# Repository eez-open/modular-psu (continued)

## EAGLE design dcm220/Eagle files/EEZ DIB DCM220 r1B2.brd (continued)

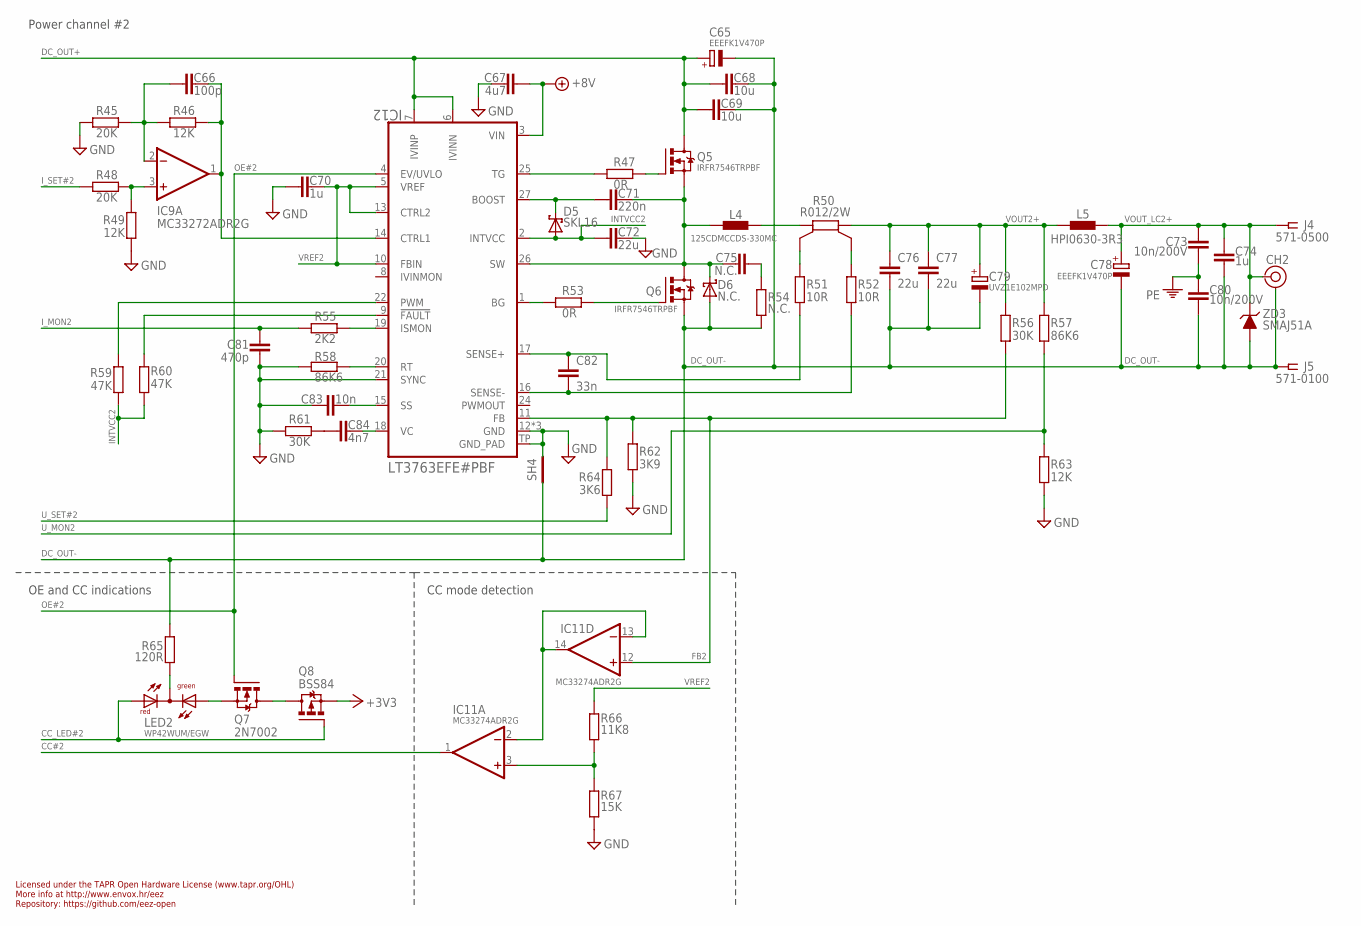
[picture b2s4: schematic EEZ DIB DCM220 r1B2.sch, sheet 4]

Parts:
C65, C78: EEEFK1V470P; CAPAE830X1050N
C66: 100p; C0805
C67: 4u7; C1206
C68, C69: 10u; C1210
C70, C74: 1u; C0805
C71: 220n; C0805
C72, C76, C77: 22u; C1210
C73, C80: 10n/200V; C1206
C75: N.C.; C0805
C79: UVZ1E102MPD; ECAP5/10.5
C81: 470p; C0805
C82: 33n; C0805
C83: 10n; C0805
C84: 4n7; C0805
CH2: TEST_POINT-2; TP_1.1MM_2
D5: SKL16; SOD123
D6: N.C.; SMA
IC9: MC33272ADR2G; SOIC127P600X173-8N
IC11: MC33274ADR2G; SOIC127P600X175-14N
IC12: LT3763EFE#PBF; LTC_05-08-1663-EB
J4: 571-0500; DELTRON_571
J5: 571-0100; DELTRON_571
L4: 125CDMCCDS-330MC; 125CDMCC/DS
L5: HPI0630-3R3; COILCRAFT_HPI0630
LED2: WP42WUM/EGW; L-42WUM-1EGWT
Q5, Q6: IRFR7546TRPBF; TO229P990X239-3N
Q7: 2N7002; SOT103P240X110-3N
Q8: BSS84; SOT95P237X112-3N
R45, R48: 20K; R0805
R46, R49, R63: 12K; R0805
R47, R53: 0R; R0805
R50: R012/2W; R_2512-4WIRE
R51, R52: 10R; R0805
R54: N.C.; R1206
R55: 2K2; R0805
R56, R61: 30K; R0805
R57, R58: 86K6; R0805
R59, R60: 47K; R0805
R62: 3K9; R0805
R64: 3K6; R0805
R65: 120R; R0805
R66: 11K8; R0805
R67: 15K; R0805
SH4: SHORTNOHOLE; SHORT_NOHOLE
ZD3: SMAJ51A; DO214AA

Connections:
+3V3: Q8.2 (S); also elsewhere on the board
+8V: C67.1, IC12.3 (VIN); also elsewhere on the board
CC#2: IC11.1 (OUT); also elsewhere on the board
CC_LED#2: LED2.RED (AR), Q8.1 (G); also elsewhere on the board
DC_OUT+: C65.+, C68.1, C69.1, IC12.6 (IVINN), IC12.7 (IVINP), Q5.2 (D); also elsewhere on the board
DC_OUT-: C65.-, C68.2, C69.2, C74.2, C76.2, C77.2, C78.-, C79.-, C80.2, CH2.GND, D6.A, J5.1, J5.1.1, Q6.3 (S), R54.1, R65.2, SH4.1 (GND_A), ZD3.A; also elsewhere on the board
FB2: IC11.12 (+IN), IC12.11 (FB), R56.1, R62.2, R64.2
GND: C67.2, C70.2, C72.2, C81.1, C83.1, IC12.12 (GND), IC12.21 (SYNC), IC12.23 (GND), IC12.28 (GND), IC12.TP (GND_PAD), R45.1, R49.1, R58.1, R61.1, R62.1, R63.1, R67.1, SH4.2 (GND_B); also elsewhere on the board
INTVCC2: C72.1, D5.A, IC12.2 (INTVCC), R59.1, R60.2
I_MON2: C81.2, R55.1; also elsewhere on the board
I_SET#2: R48.1; also elsewhere on the board
LOUT2: L4.2, R50.1
unnamed: IC12.20 (RT), R58.2
unnamed: LED2.CC (C), R65.1
unnamed: C83.2, IC12.15 (SS)
unnamed: C84.1, R61.2
unnamed: Q7.3 (D), Q8.3 (D)
unnamed: LED2.GREEN (AG), Q7.2 (S)
unnamed: C84.2, IC12.18 (VC)
unnamed: IC12.9 (!FAULT), R60.1
unnamed: IC12.25 (TG), R47.1
unnamed: Q5.1 (G), R47.2
unnamed: IC12.1 (BG), R53.1
unnamed: Q6.1 (G), R53.2
unnamed: R50.1S, R51.2
unnamed: R50.2S, R52.2
unnamed: C75.2, R54.2
unnamed: C71.1, D5.C, IC12.27 (BOOST)
unnamed: IC12.19 (ISMON), R55.2
unnamed: IC11.2 (-IN), IC11.13 (-IN), IC11.14 (OUT)
unnamed: IC11.3 (+IN), R66.1, R67.2
unnamed: C66.1, IC9.1 (OUT), IC12.14 (CTRL1), R46.2
unnamed: C66.2, IC9.2 (-IN), R45.2, R46.1
unnamed: IC9.3 (+IN), R48.2, R49.2
OE#2: IC12.4 (EV/UVLO), Q7.1 (G); also elsewhere on the board
PE: C73.1, C80.1; also elsewhere on the board
PWM#2: IC12.22 (PWM), R59.2
SENSE1+1: C82.1, IC12.17 (SENSE+), R51.1
SENSE1-1: C82.2, IC12.16 (SENSE-), R52.1
SW2: C71.2, C75.1, D6.C, IC12.26 (SW), L4.1, Q5.3 (S), Q6.2 (D)
U_MON2: R57.1, R63.2; also elsewhere on the board
U_SET#2: R64.1; also elsewhere on the board
VOUT2+: C76.1, C77.1, C79.+, L5.1, R50.2, R56.2, R57.2
VOUT_LC2+: C73.2, C74.1, C78.+, CH2.TIP, J4.1, J4.1.1, L5.2, ZD3.C
VREF2: C70.1, IC12.5 (VREF), IC12.10 (FBIN), IC12.13 (CTRL2), R66.2

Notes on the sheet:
Licensed under the TAPR Open Hardware License (www.tapr.org/OHL)
Repository: https://github.com/eez-open
More info at http://www.envox.hr/eez
CC mode detection
OE and CC indications
Power channel #2

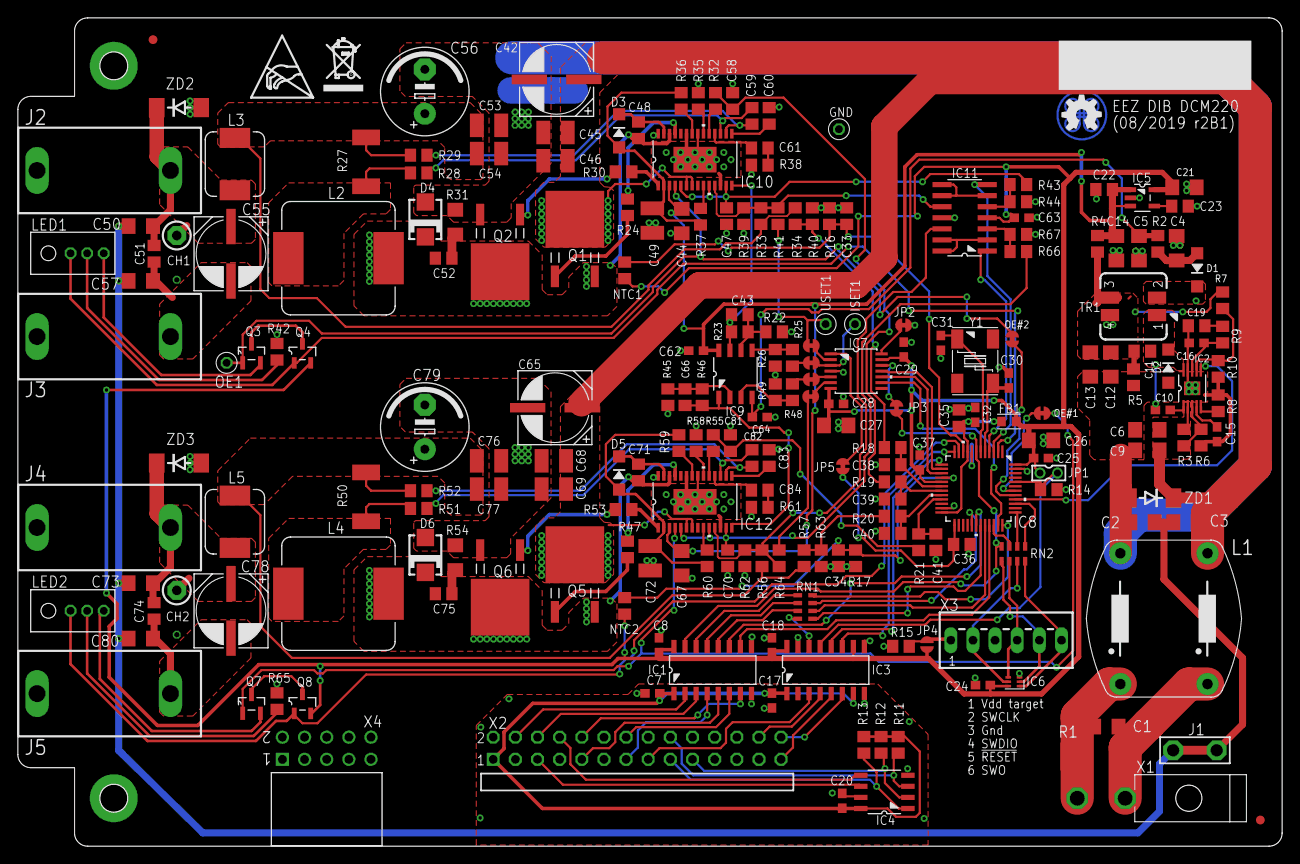
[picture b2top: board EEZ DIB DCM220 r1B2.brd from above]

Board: 2 copper layers, 145.0 x 95.0 mm, 231 parts (1 on the bottom side), 165 nets.

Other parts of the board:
EEZ_SIGNATURE: SIGNATURESMALL; SIGNATURE_5MM
U$2: RECYCLE_BIN1/8
U$4: ESD_SYMBOL

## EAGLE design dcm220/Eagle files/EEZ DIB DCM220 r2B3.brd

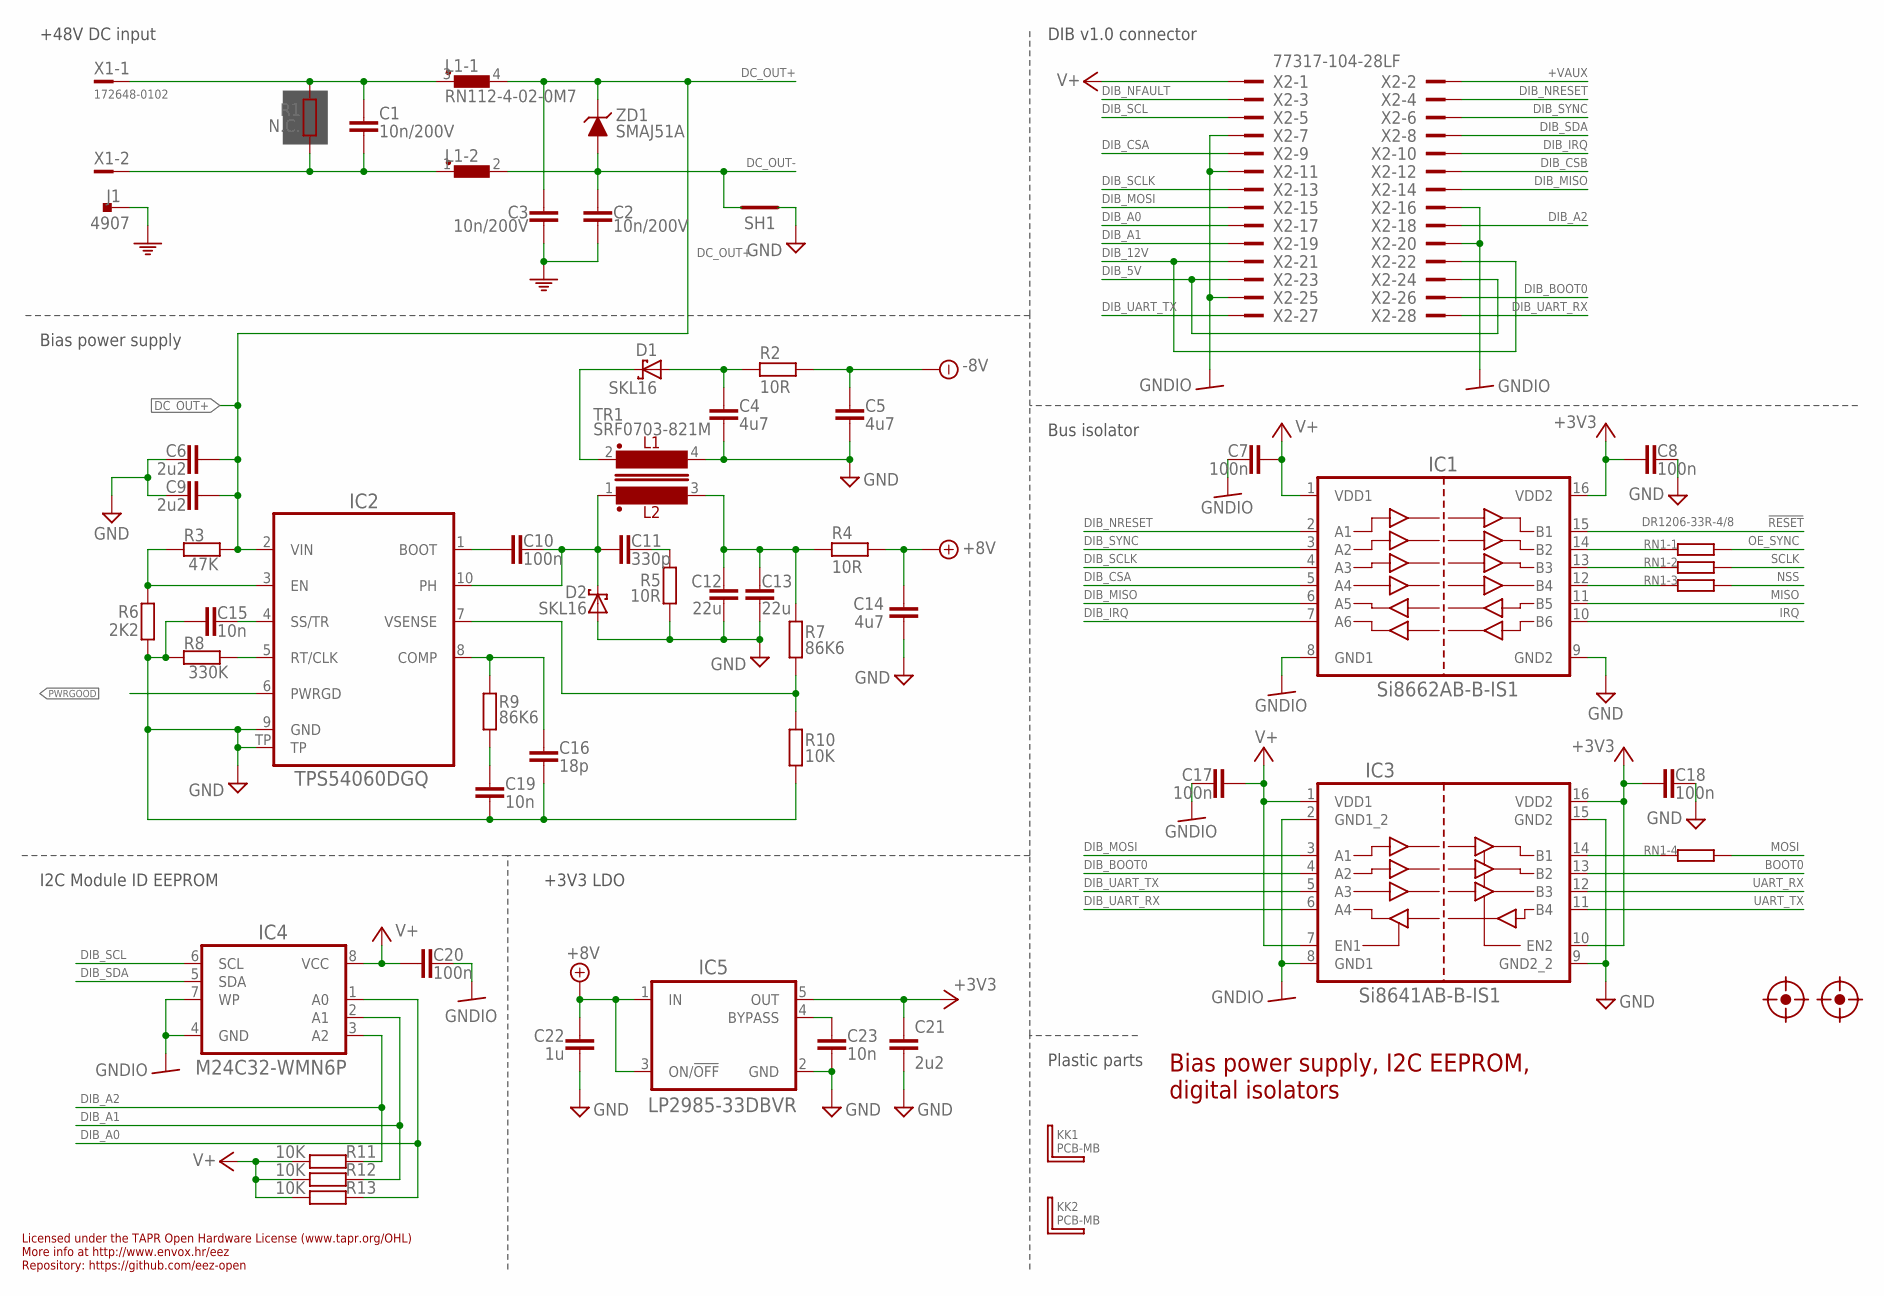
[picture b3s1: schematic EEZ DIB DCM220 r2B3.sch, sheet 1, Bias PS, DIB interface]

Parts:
C1, C2, C3: 10n/200V; C1206
C4, C5, C14: 4u7; C1206
C6, C9, C21: 2u2; C1206
C7, C8, C10, C17, C18, C20: 100n; C0603
C11: 330p; C0805
C12, C13: 22u; C1206
C15, C19, C23: 10n; C0805
C16: 18p; C0603
C22: 1u; C0805
D1, D2: SKL16; SOD123
FM1, FM2: FIDUCIAL_2; FIDUCIAL_DUAL
IC1: Si8662AB-B-IS1; SOIC-16
IC2: TPS54060DGQ; SOP50P490X110-11N
IC3: Si8641AB-B-IS1; SOIC-16
IC4: M24C32-WMN6P; SOIC127P600X173-8N
IC5: LP2985-33DBVR; SOT95P270X145-5N
J1: 4907; PCB_TAB-4907
KK1, KK2: PCB-MB
L1: RN112-4-02-0M7; RN112
R1: N.C.; R2512
R2, R4, R5: 10R; R0805
R3: 47K; R0805
R6: 2K2; R0805
R7, R9: 86K6; R0805
R8: 330K; R0805
R10, R11, R12, R13: 10K; R0805
RN1: DR1206-33R-4/8; CAY16
SH1: SHORTNOHOLE; SHORT_NOHOLE
TR1: SRF0703-821M; SRF0703
X1: 172648-0102; MINIFIT_39301020
X2: 77317-104-28LF
ZD1: SMAJ51A; DO214AA

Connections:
!RESET: IC1.15 (B1); also elsewhere on the board
+3V3: C8.2, C18.2, C21.1, IC1.16 (VDD2), IC3.10 (EN2), IC3.16 (VDD2), IC5.5 (OUT); also elsewhere on the board
+8V: C14.1, C22.2, IC5.1 (IN), IC5.3 (ON/!OFF), R4.1; also elsewhere on the board
+VAUX: X2.2
-8V: C5.1, R2.1; also elsewhere on the board
BOOT0: IC3.13 (B2); also elsewhere on the board
DC+: C1.2, L1.3 (1), R1.2, X1.1
DC-: C1.1, L1.1, R1.1, X1.2
DC_OUT+: C3.2, C6.1, C9.1, IC2.2 (VIN), L1.4 (2), R3.2, ZD1.C; also elsewhere on the board
DC_OUT-: C2.1, L1.2, SH1.2 (GND_B), ZD1.A; also elsewhere on the board
DIB_5V: X2.23, X2.24
DIB_12V: X2.21, X2.22
DIB_A0: IC4.1 (A0), R13.2, X2.17
DIB_A1: IC4.2 (A1), R12.2, X2.19
DIB_A2: IC4.3 (A2), R11.2, X2.18
DIB_BOOT0: IC3.4 (A2), X2.26
DIB_CSA: IC1.5 (A4), X2.9
DIB_CSB: X2.12
DIB_IRQ: IC1.7 (A6), X2.10
DIB_MISO: IC1.6 (A5), X2.14
DIB_MOSI: IC3.3 (A1), X2.15
DIB_NFAULT: X2.3
DIB_NRESET: IC1.2 (A1), X2.4
DIB_SCL: IC4.6 (SCL), X2.5
DIB_SCLK: IC1.4 (A3), X2.13
DIB_SDA: IC4.5 (SDA), X2.8
DIB_SYNC: IC1.3 (A2), X2.6
DIB_UART_RX: IC3.6 (A4), X2.28
DIB_UART_TX: IC3.5 (A3), X2.27
GND: C4.2, C5.2, C6.2, C8.1, C9.2, C12.2, C13.2, C14.2, C15.2, C16.1, C18.1, C19.1, C21.2, C22.1, C23.1, D2.A, IC1.9 (GND2), IC2.9 (GND), IC2.TP, IC3.9 (GND2_2), IC3.15 (GND2), IC5.2 (GND), R5.1, R6.1, R8.1, R10.1, SH1.1 (GND_A), TR1.4; also elsewhere on the board
GNDIO: C7.2, C17.2, C20.1, IC1.8 (GND1), IC3.2 (GND1_2), IC3.8 (GND1), IC4.4 (GND), IC4.7 (WP), X2.7, X2.11, X2.16, X2.20, X2.25
IRQ: IC1.10 (B6); also elsewhere on the board
MISO: IC1.11 (B5); also elsewhere on the board
MOSI: RN1.5 (2); also elsewhere on the board
unnamed: IC1.14 (B2), RN1.1
unnamed: IC1.13 (B3), RN1.2 (1)
unnamed: IC1.12 (B4), RN1.3 (1)
unnamed: IC3.14 (B1), RN1.4 (1)
unnamed: C23.2, IC5.4 (BYPASS)
unnamed: C4.1, D1.A, R2.2
unnamed: C11.2, R5.2
unnamed: IC2.3 (EN), R3.1, R6.2
unnamed: C15.1, IC2.4 (SS/TR)
unnamed: IC2.5 (RT/CLK), R8.2
unnamed: C16.2, IC2.8 (COMP), R9.2
unnamed: C19.2, R9.1
unnamed: C10.2, IC2.1 (BOOT)
unnamed: IC2.7 (VSENSE), R7.1, R10.2
NSS: RN1.6 (2); also elsewhere on the board
OE_SYNC: RN1.8 (2); also elsewhere on the board
PE: C2.2, C3.1, J1.1, J1.2; also elsewhere on the board
PH1: C10.1, C11.1, D2.C, IC2.10 (PH), TR1.1
PWRGOOD: IC2.6 (PWRGD); also elsewhere on the board
SCLK: RN1.7 (2); also elsewhere on the board
UART_RX: IC3.12 (B3); also elsewhere on the board
UART_TX: IC3.11 (B4); also elsewhere on the board
V+: C7.1, C17.1, C20.2, IC1.1 (VDD1), IC3.1 (VDD1), IC3.7 (EN1), IC4.8 (VCC), R11.1, R12.1, R13.1, X2.1
VOUT+: C12.1, C13.1, R4.2, R7.2, TR1.3
VOUT-: D1.C, TR1.2

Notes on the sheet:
Licensed under the TAPR Open Hardware License (www.tapr.org/OHL)
Repository: https://github.com/eez-open
More info at http://www.envox.hr/eez
I2C Module ID EEPROM
Bias power supply, I2C EEPROM, digital isolators
Plastic parts
Bus isolator
+3V3 LDO
DIB v1.0 connector
Bias power supply
+48V DC input

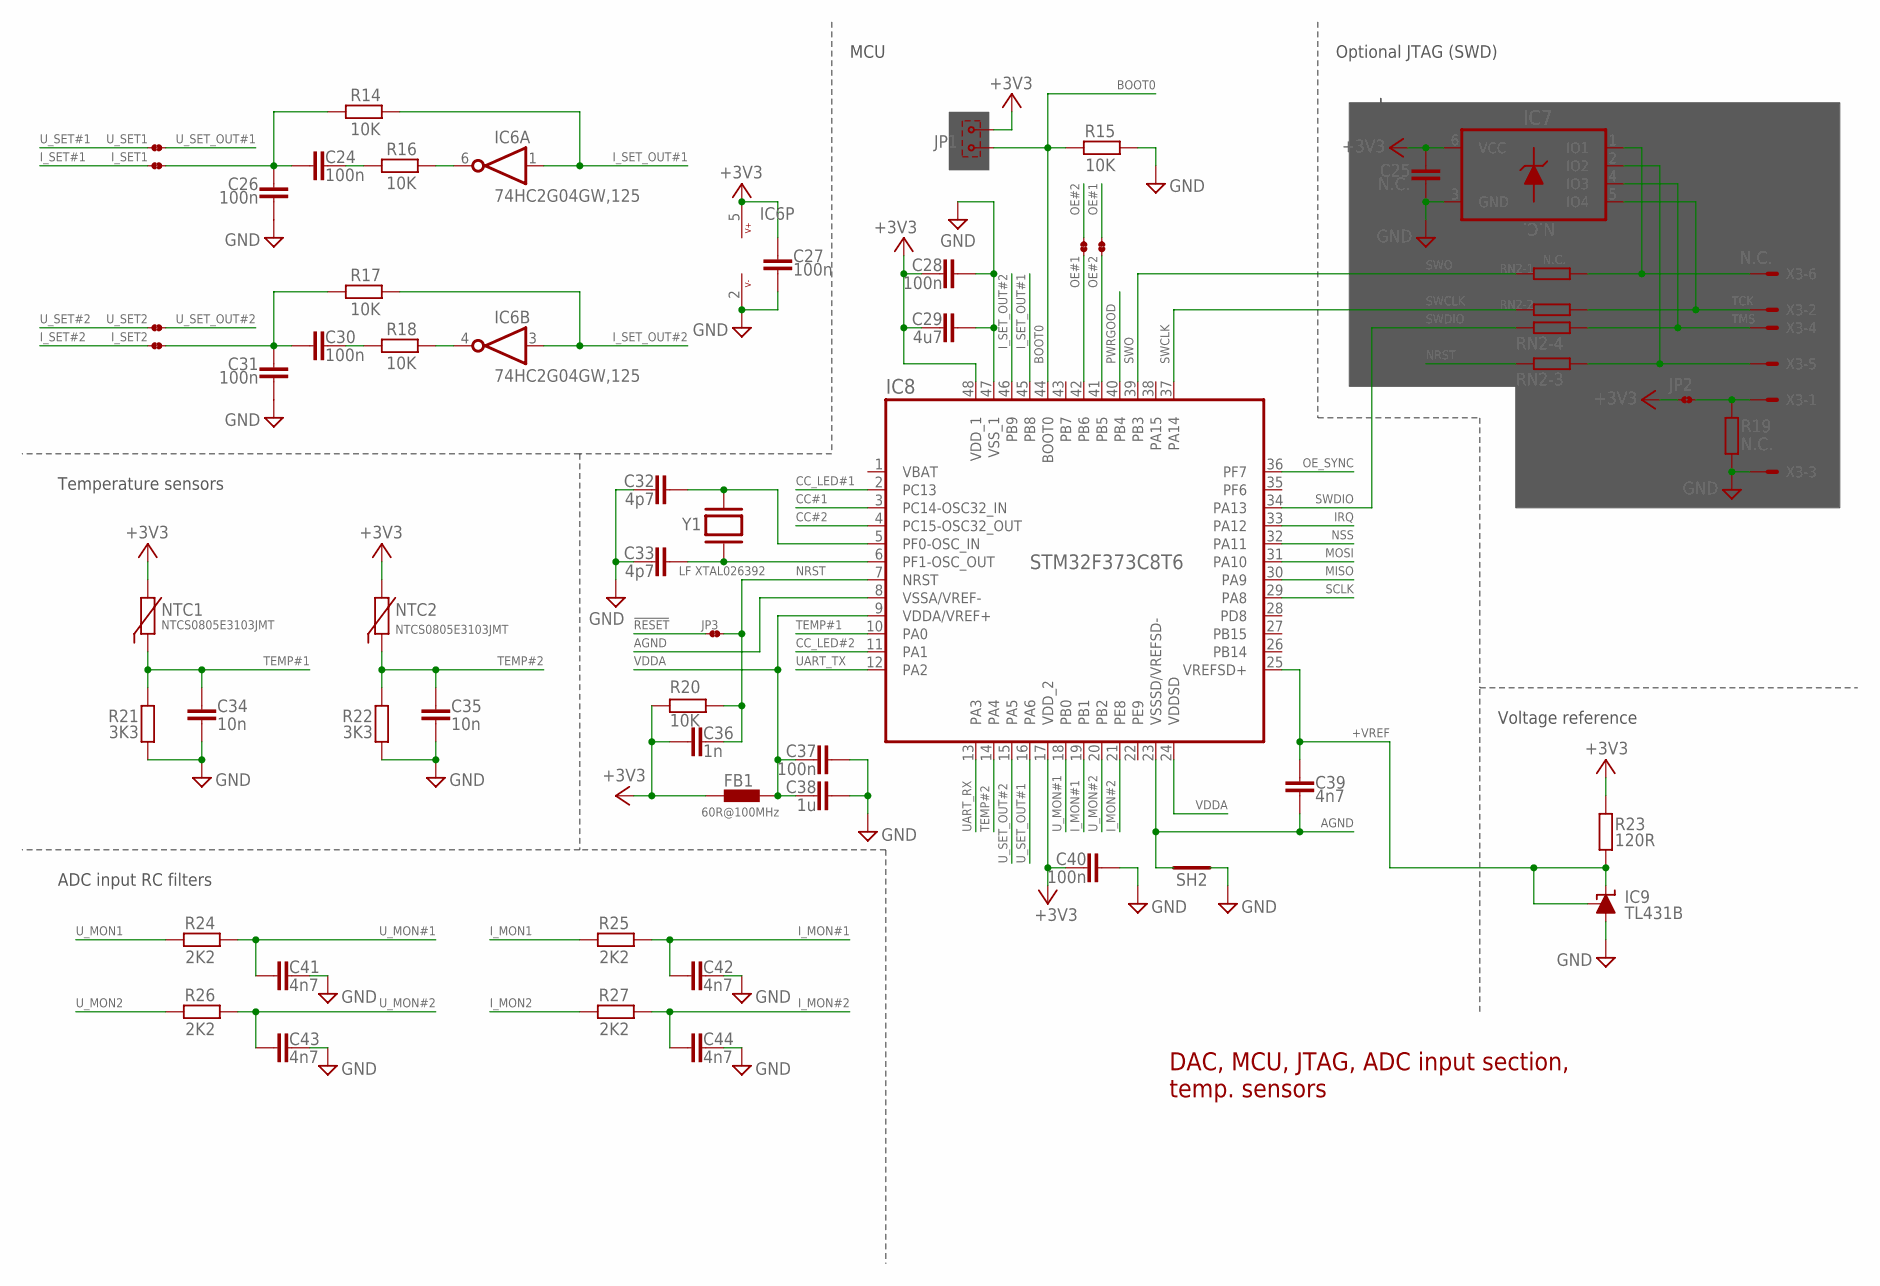
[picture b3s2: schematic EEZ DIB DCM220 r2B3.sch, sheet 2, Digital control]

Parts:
C24, C26, C27, C28, C30, C31, C37, C40: 100n; C0603
C25: N.C.; C0603
C29: 4u7; C1206
C32, C33: 4p7; C0603
C34, C35: 10n; C0805
C36: 1n; C0805
C38: 1u; C0805
C39, C41, C42, C43, C44: 4n7; C0805
FB1: 60R@100MHz; BEAD0603
IC6: 74HC2G04GW,125; SOT65P210X110-6N
IC7: N.C.; DRL6
IC8: STM32F373C8T6; LQFP-48
IC9: TL431B; SOT103P240X110-3N
I_SET1, I_SET2: JP2-NOCUT
JP1: JUMPER-2PIN-2MM; 2MM-2
JP2: JP2-CUT
JP3: JP2-NOCUT
NTC1, NTC2: NTCS0805E3103JMT; R_0805
OE#1, OE#2: JP2-NOCUT
R14, R15, R16, R17, R18, R20: 10K; R0805
R19: N.C.; R0805
R21, R22: 3K3; R0805
R23: 120R; R0805
R24, R25, R26, R27: 2K2; R0805
RN2: N.C.; CAY16
SH2: SHORTNOHOLE; SHORT_NOHOLE
U_SET1, U_SET2: JP2-NOCUT
X3: N.C.; 22-23-2061
Y1: LF XTAL026392; 12SMX(B)

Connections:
!RESET: JP3.1; also elsewhere on the board
+3V3: C25.1, C27.1, C28.2, C29.1, C36.2, C40.2, FB1.P$1 (1), IC6.5 (V+), IC7.6 (VCC), IC8.17 (VDD_2), IC8.48 (VDD_1), JP1.1, JP2.1, NTC1.1, NTC2.1, R20.1, R23.1; also elsewhere on the board
+VREF: C39.2, IC8.25 (VREFSD+), IC9.1 (C), IC9.2 (R), R23.2
AGND: C39.1, IC8.8 (VSSA/VREF-), IC8.23 (VSSSD/VREFSD-), SH2.1 (GND_A)
BOOT0: IC8.44 (BOOT0), JP1.2, R15.2; also elsewhere on the board
CC#1: IC8.3 (PC14-OSC32_IN); also elsewhere on the board
CC#2: IC8.4 (PC15-OSC32_OUT); also elsewhere on the board
CC_LED#1: IC8.2 (PC13); also elsewhere on the board
CC_LED#2: IC8.11 (PA1); also elsewhere on the board
GND: C25.2, C26.2, C27.2, C28.1, C29.2, C31.2, C32.1, C33.1, C34.1, C35.1, C37.1, C38.1, C40.1, C41.1, C42.1, C43.1, C44.1, IC6.2 (V-), IC7.3 (GND), IC8.47 (VSS_1), IC9.3 (A), R15.1, R19.1, R21.2, R22.2, SH2.2 (GND_B), X3.3; also elsewhere on the board
IRQ: IC8.33 (PA12); also elsewhere on the board
I_MON1: R25.2; also elsewhere on the board
I_MON2: R27.2; also elsewhere on the board
I_MON#1: C42.2, IC8.19 (PB1), R25.1
I_MON#2: C44.2, IC8.21 (PE8), R27.1
I_SET#1: I_SET1.1; also elsewhere on the board
I_SET#2: I_SET2.1; also elsewhere on the board
I_SET_OUT#1: IC6.1 (I), IC8.45 (PB8), R14.2
I_SET_OUT#2: IC6.3 (I), IC8.46 (PB9), R17.2
MISO: IC8.30 (PA9); also elsewhere on the board
MOSI: IC8.31 (PA10); also elsewhere on the board
unnamed: C30.2, R18.1
unnamed: C30.1, C31.1, I_SET2.2, R17.1
unnamed: IC6.4 (O), R18.2
unnamed: IC7.1 (IO1), RN2.8 (2), X3.6
unnamed: IC7.2 (IO2), RN2.6 (2), X3.5
unnamed: JP2.2, R19.2, X3.1
unnamed: C24.2, R16.1
unnamed: C24.1, C26.1, I_SET1.2, R14.1
unnamed: IC6.6 (O), R16.2
unnamed: IC8.42 (PB6), OE#1.1
unnamed: IC8.41 (PB5), OE#2.1
NRST: C36.1, IC8.7 (NRST), JP3.2, R20.2, RN2.3 (1)
NSS: IC8.32 (PA11); also elsewhere on the board
OE#1: OE#2.2; also elsewhere on the board
OE#2: OE#1.2; also elsewhere on the board
OE_SYNC: IC8.36 (PF7); also elsewhere on the board
PWRGOOD: IC8.40 (PB4); also elsewhere on the board
RCC_OSC_IN: C32.2, IC8.5 (PF0-OSC_IN), Y1.3 (2)
RCC_OSC_OUT: C33.2, IC8.6 (PF1-OSC_OUT), Y1.1
SCLK: IC8.29 (PA8); also elsewhere on the board
SWCLK: IC8.37 (PA14), RN2.2 (1)
SWDIO: IC8.34 (PA13), RN2.4 (1)
SWO: IC8.39 (PB3), RN2.1
TCK: IC7.5 (IO4), RN2.7 (2), X3.2
TEMP#1: C34.2, IC8.10 (PA0), NTC1.2, R21.1
TEMP#2: C35.2, IC8.14 (PA4), NTC2.2, R22.1
TMS: IC7.4 (IO3), RN2.5 (2), X3.4
UART_RX: IC8.13 (PA3); also elsewhere on the board
UART_TX: IC8.12 (PA2); also elsewhere on the board
U_MON1: R24.2; also elsewhere on the board
U_MON2: R26.2; also elsewhere on the board
U_MON#1: C41.2, IC8.18 (PB0), R24.1
U_MON#2: C43.2, IC8.20 (PB2), R26.1
U_SET#1: U_SET1.1; also elsewhere on the board
U_SET#2: U_SET2.1; also elsewhere on the board
U_SET_OUT#1: IC8.16 (PA6), U_SET1.2
U_SET_OUT#2: IC8.15 (PA5), U_SET2.2
VDDA: C37.2, C38.2, FB1.P$2 (2), IC8.9 (VDDA/VREF+), IC8.24 (VDDSD)

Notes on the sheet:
DAC, MCU, JTAG, ADC input section, temp. sensors
Optional JTAG (SWD)
MCU
Temperature sensors
ADC input RC filters
Voltage reference

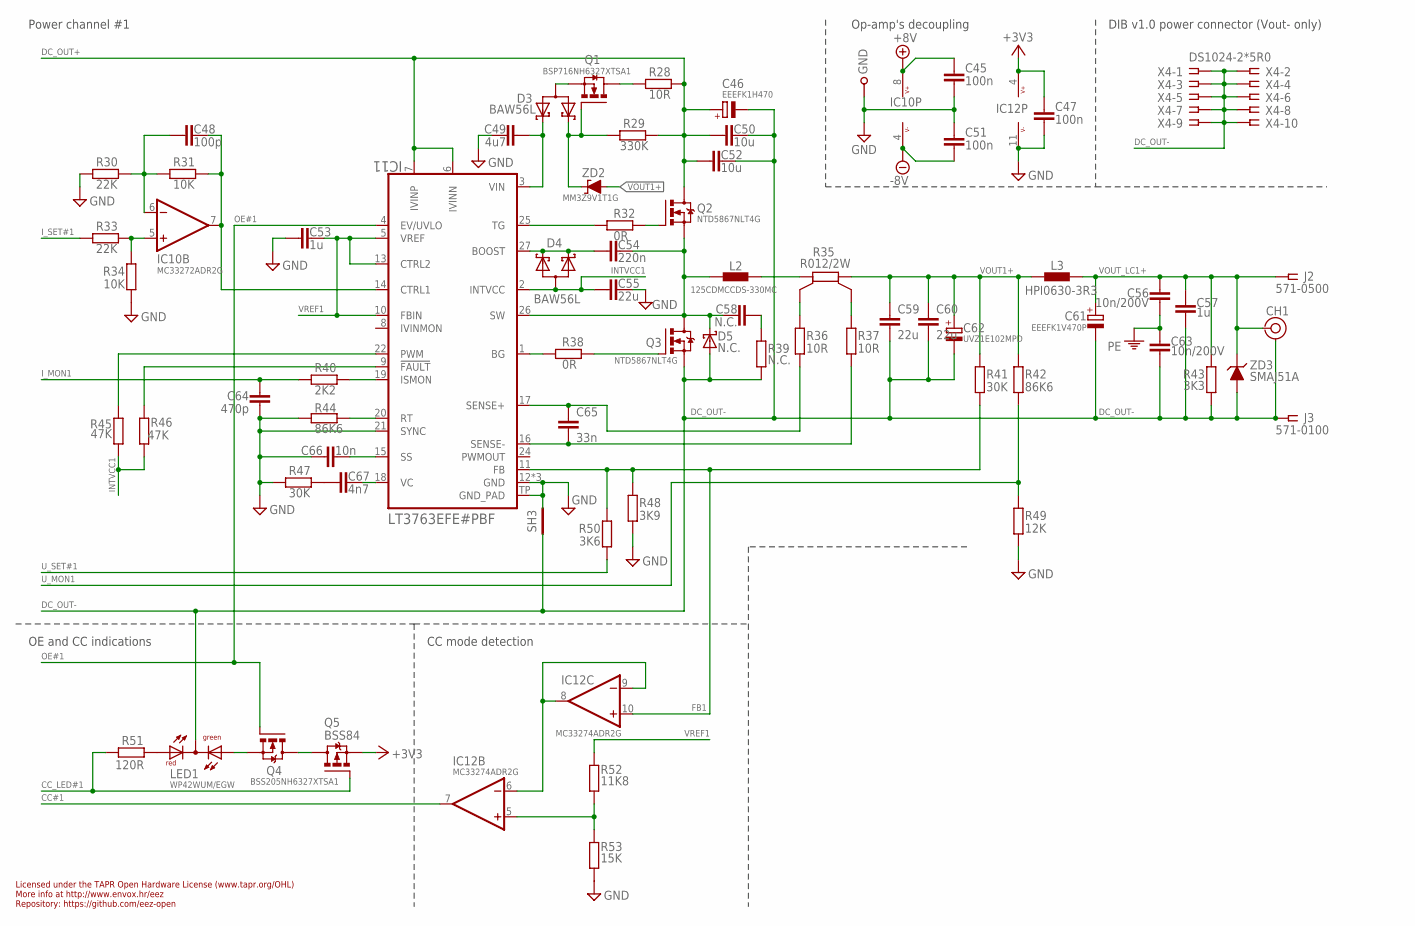
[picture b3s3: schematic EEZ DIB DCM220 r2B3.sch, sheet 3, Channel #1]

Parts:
C45, C47, C51: 100n; C0603
C46: EEEFK1H470; CAPAE830X1050N
C48: 100p; C0805
C49: 4u7; C1206
C50, C52: 10u; C1210
C53, C57: 1u; C0805
C54: 220n; C0805
C55, C59, C60: 22u; C1210
C56, C63: 10n/200V; C1206
C58: N.C.; C0805
C61: EEEFK1V470P; CAPAE660X610N
C62: UVZ1E102MPD; ECAP5/10.5
C64: 470p; C0805
C65: 33n; C0805
C66: 10n; C0805
C67: 4n7; C0805
CH1: TEST_POINT-2; TP_1.1MM_2
D3, D4: BAW56L; SOT23
D5: N.C.; SMA
GND: TEST-PIN_0.9MM
IC10: MC33272ADR2G; SOIC127P600X173-8N
IC11: LT3763EFE#PBF; LTC_05-08-1663-EB
IC12: MC33274ADR2G; SOIC127P600X175-14N
J2: 571-0500; DELTRON_571
J3: 571-0100; DELTRON_571
L2: 125CDMCCDS-330MC; 125CDMCC/DS
L3: HPI0630-3R3; COILCRAFT_HPI0630
LED1: WP42WUM/EGW; L-42WUM-1EGWT
Q1: BSP716NH6327XTSA1; SOT223
Q2, Q3: NTD5867NLT4G; TO229P990X239-3N
Q4: BSS205NH6327XTSA1; SOT103P240X110-3N
Q5: BSS84; SOT95P237X112-3N
R28, R36, R37: 10R; R0805
R29: 330K; R0805
R30, R33: 22K; R0805
R31, R34: 10K; R0805
R32, R38: 0R; R0805
R35: R012/2W; R_2512-4WIRE
R39: N.C.; R1206
R40: 2K2; R0805
R41, R47: 30K; R0805
R42, R44: 86K6; R0805
R43: 3K3; R0805
R45, R46: 47K; R0805
R48: 3K9; R0805
R49: 12K; R0805
R50: 3K6; R0805
R51: 120R; R0805
R52: 11K8; R0805
R53: 15K; R0805
SH3: SHORTNOHOLE; SHORT_NOHOLE
X4: DS1024-2*5R0; SSW-105-02-T-D-RA
ZD2: MM3Z9V1T1G; SOD323-W
ZD3: SMAJ51A; DO214AA

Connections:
+3V3: C47.1, IC12.4 (V+), Q5.2 (S); also elsewhere on the board
+8V: C45.1, IC10.8 (V+); also elsewhere on the board
-8V: C51.2, IC10.4 (V-); also elsewhere on the board
CC#1: IC12.7 (OUT); also elsewhere on the board
CC_LED#1: Q5.1 (G), R51.2; also elsewhere on the board
DC_OUT+: C46.+, C50.1, C52.1, IC11.6 (IVINN), IC11.7 (IVINP), Q2.2 (D), R28.1, R29.1; also elsewhere on the board
DC_OUT-: C46.-, C50.2, C52.2, C57.2, C59.2, C60.2, C61.2 (-), C62.-, C63.2, CH1.GND, D5.A, J3.1, J3.1.1, LED1.CC (C), Q3.3 (S), R39.1, R43.2, SH3.1 (GND_A), X4.1, X4.2, X4.3, X4.4, X4.5, X4.6, X4.7, X4.8, X4.9, X4.10, ZD3.A; also elsewhere on the board
FB1: IC11.11 (FB), IC12.10 (+IN), R41.1, R48.2, R50.2
GND: C45.2, C47.2, C49.2, C51.1, C53.2, C55.2, C64.1, C66.1, GND.1, IC11.12 (GND), IC11.21 (SYNC), IC11.23 (GND), IC11.28 (GND), IC11.TP (GND_PAD), IC12.11 (V-), R30.1, R34.1, R44.1, R47.1, R48.1, R49.1, R53.1, SH3.2 (GND_B); also elsewhere on the board
INTVCC1: C55.1, D4.3 (CA), IC11.2 (INTVCC), R45.1, R46.2
ISET1: C48.1, IC10.7 (OUT), IC11.14 (CTRL1), R31.2
I_MON1: C64.2, R40.1; also elsewhere on the board
I_SET#1: R33.1; also elsewhere on the board
LOUT1: L2.2, R35.1
unnamed: IC11.1 (BG), R38.1
unnamed: Q3.1 (G), R38.2
unnamed: Q4.3 (D), Q5.3 (D)
unnamed: R35.1S, R36.2
unnamed: IC11.20 (RT), R44.2
unnamed: LED1.RED (AR), R51.1
unnamed: C66.2, IC11.15 (SS)
unnamed: C67.1, R47.2
unnamed: C67.2, IC11.18 (VC)
unnamed: IC11.25 (TG), R32.1
unnamed: R35.2S, R37.2
unnamed: C58.2, R39.2
unnamed: IC11.9 (!FAULT), R46.1
unnamed: Q2.1 (G), R32.2
unnamed: C54.1, D4.1 (K1), D4.2 (K2), IC11.27 (BOOST)
unnamed: D3.1 (K1), Q1.1 (G), R29.2, ZD2.C
unnamed: LED1.GREEN (AG), Q4.2 (S)
unnamed: C49.1, D3.2 (K2), IC11.3 (VIN)
unnamed: D3.3 (CA), Q1.3 (S)
unnamed: IC11.19 (ISMON), R40.2
unnamed: IC12.5 (+IN), R52.1, R53.2
unnamed: IC12.6 (-IN), IC12.8 (OUT), IC12.9 (-IN)
unnamed: IC10.5 (+IN), R33.2, R34.2
unnamed: C48.2, IC10.6 (-IN), R30.2, R31.1
OE#1: IC11.4 (EV/UVLO), Q4.1 (G); also elsewhere on the board
PE: C56.1, C63.1; also elsewhere on the board
PWM#1: IC11.22 (PWM), R45.2
Q1D: Q1.2 (D), Q1.4 (D), R28.2
SENSE1+: C65.1, IC11.17 (SENSE+), R36.1
SENSE1-: C65.2, IC11.16 (SENSE-), R37.1
SW1: C54.2, C58.1, D5.C, IC11.26 (SW), L2.1, Q2.3 (S), Q3.2 (D)
U_MON1: R42.1, R49.2; also elsewhere on the board
U_SET#1: R50.1; also elsewhere on the board
VOUT1+: C59.1, C60.1, C62.+, L3.1, R35.2, R41.2, R42.2, ZD2.A
VOUT_LC1+: C56.2, C57.1, C61.1 (+), CH1.TIP, J2.1, J2.1.1, L3.2, R43.1, ZD3.C
VREF1: C53.1, IC11.5 (VREF), IC11.10 (FBIN), IC11.13 (CTRL2), R52.2

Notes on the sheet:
Licensed under the TAPR Open Hardware License (www.tapr.org/OHL)
Repository: https://github.com/eez-open
More info at http://www.envox.hr/eez
Power channel #1
CC mode detection
DIB v1.0 power connector (Vout- only)
Op-amp's decoupling
OE and CC indications

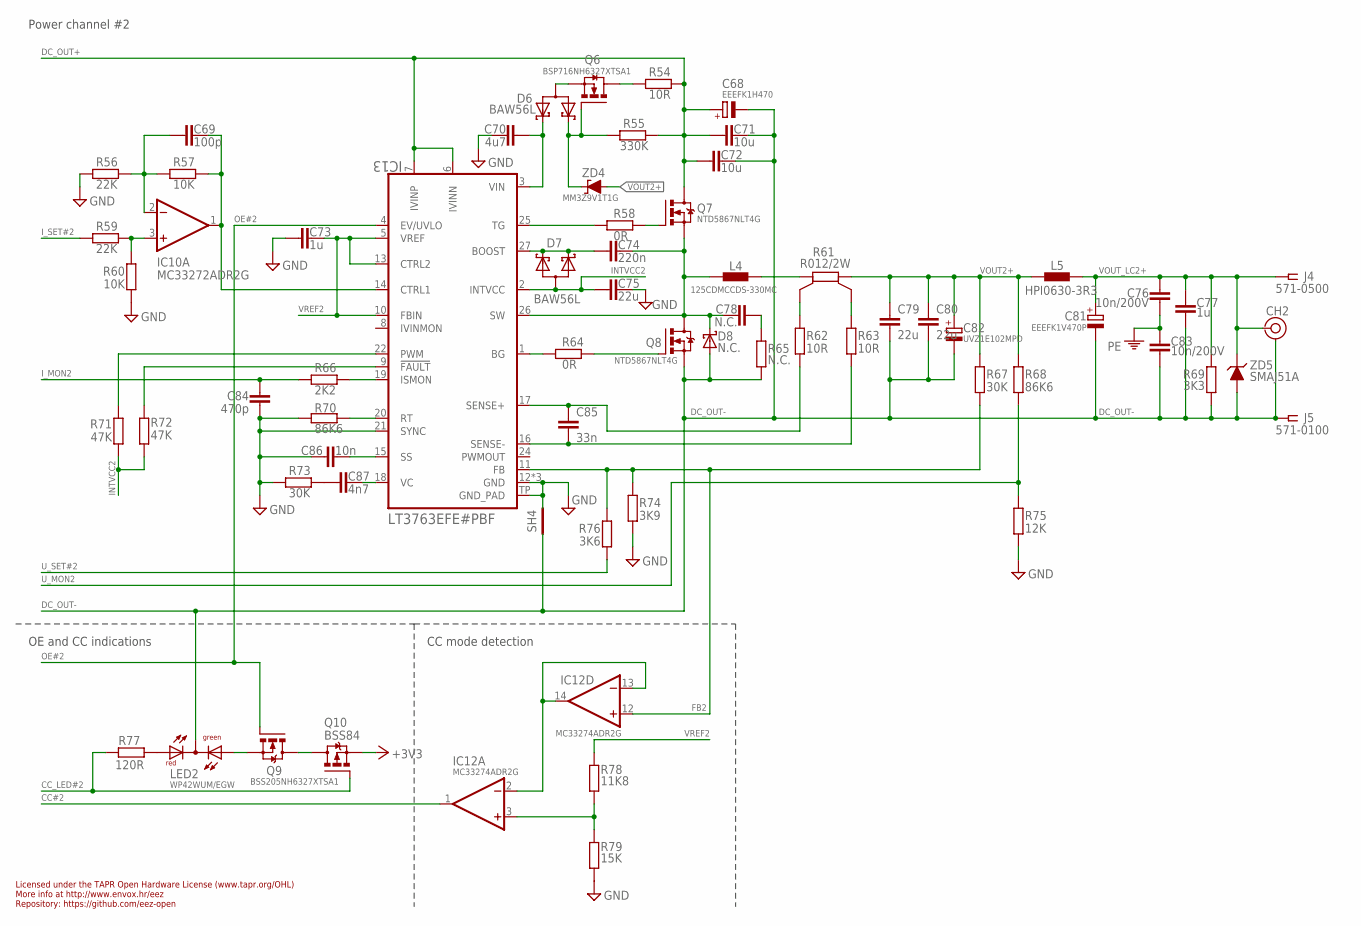
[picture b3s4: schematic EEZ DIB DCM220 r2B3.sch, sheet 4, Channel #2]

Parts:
C68: EEEFK1H470; CAPAE830X1050N
C69: 100p; C0805
C70: 4u7; C1206
C71, C72: 10u; C1210
C73, C77: 1u; C0805
C74: 220n; C0805
C75, C79, C80: 22u; C1210
C76, C83: 10n/200V; C1206
C78: N.C.; C0805
C81: EEEFK1V470P; CAPAE660X610N
C82: UVZ1E102MPD; ECAP5/10.5
C84: 470p; C0805
C85: 33n; C0805
C86: 10n; C0805
C87: 4n7; C0805
CH2: TEST_POINT-2; TP_1.1MM_2
D6, D7: BAW56L; SOT23
D8: N.C.; SMA
IC10: MC33272ADR2G; SOIC127P600X173-8N
IC12: MC33274ADR2G; SOIC127P600X175-14N
IC13: LT3763EFE#PBF; LTC_05-08-1663-EB
J4: 571-0500; DELTRON_571
J5: 571-0100; DELTRON_571
L4: 125CDMCCDS-330MC; 125CDMCC/DS
L5: HPI0630-3R3; COILCRAFT_HPI0630
LED2: WP42WUM/EGW; L-42WUM-1EGWT
Q6: BSP716NH6327XTSA1; SOT223
Q7, Q8: NTD5867NLT4G; TO229P990X239-3N
Q9: BSS205NH6327XTSA1; SOT103P240X110-3N
Q10: BSS84; SOT95P237X112-3N
R54, R62, R63: 10R; R0805
R55: 330K; R0805
R56, R59: 22K; R0805
R57, R60: 10K; R0805
R58, R64: 0R; R0805
R61: R012/2W; R_2512-4WIRE
R65: N.C.; R1206
R66: 2K2; R0805
R67, R73: 30K; R0805
R68, R70: 86K6; R0805
R69: 3K3; R0805
R71, R72: 47K; R0805
R74: 3K9; R0805
R75: 12K; R0805
R76: 3K6; R0805
R77: 120R; R0805
R78: 11K8; R0805
R79: 15K; R0805
SH4: SHORTNOHOLE; SHORT_NOHOLE
ZD4: MM3Z9V1T1G; SOD323-W
ZD5: SMAJ51A; DO214AA

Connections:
+3V3: Q10.2 (S); also elsewhere on the board
CC#2: IC12.1 (OUT); also elsewhere on the board
CC_LED#2: Q10.1 (G), R77.2; also elsewhere on the board
DC_OUT+: C68.+, C71.1, C72.1, IC13.6 (IVINN), IC13.7 (IVINP), Q7.2 (D), R54.1, R55.1; also elsewhere on the board
DC_OUT-: C68.-, C71.2, C72.2, C77.2, C79.2, C80.2, C81.2 (-), C82.-, C83.2, CH2.GND, D8.A, J5.1, J5.1.1, LED2.CC (C), Q8.3 (S), R65.1, R69.2, SH4.1 (GND_A), ZD5.A; also elsewhere on the board
FB2: IC12.12 (+IN), IC13.11 (FB), R67.1, R74.2, R76.2
GND: C70.2, C73.2, C75.2, C84.1, C86.1, IC13.12 (GND), IC13.21 (SYNC), IC13.23 (GND), IC13.28 (GND), IC13.TP (GND_PAD), R56.1, R60.1, R70.1, R73.1, R74.1, R75.1, R79.1, SH4.2 (GND_B); also elsewhere on the board
INTVCC2: C75.1, D7.3 (CA), IC13.2 (INTVCC), R71.1, R72.2
ISET2: C69.1, IC10.1 (OUT), IC13.14 (CTRL1), R57.2
I_MON2: C84.2, R66.1; also elsewhere on the board
I_SET#2: R59.1; also elsewhere on the board
LOUT2: L4.2, R61.1
unnamed: LED2.RED (AR), R77.1
unnamed: IC13.20 (RT), R70.2
unnamed: C86.2, IC13.15 (SS)
unnamed: C87.1, R73.2
unnamed: Q9.3 (D), Q10.3 (D)
unnamed: LED2.GREEN (AG), Q9.2 (S)
unnamed: C70.1, D6.2 (K2), IC13.3 (VIN)
unnamed: D6.1 (K1), Q6.1 (G), R55.2, ZD4.C
unnamed: D6.3 (CA), Q6.3 (S)
unnamed: C87.2, IC13.18 (VC)
unnamed: IC13.9 (!FAULT), R72.1
unnamed: IC13.25 (TG), R58.1
unnamed: Q7.1 (G), R58.2
unnamed: IC13.1 (BG), R64.1
unnamed: Q8.1 (G), R64.2
unnamed: R61.1S, R62.2
unnamed: R61.2S, R63.2
unnamed: C78.2, R65.2
unnamed: C74.1, D7.1 (K1), D7.2 (K2), IC13.27 (BOOST)
unnamed: IC13.19 (ISMON), R66.2
unnamed: IC12.2 (-IN), IC12.13 (-IN), IC12.14 (OUT)
unnamed: IC12.3 (+IN), R78.1, R79.2
unnamed: C69.2, IC10.2 (-IN), R56.2, R57.1
unnamed: IC10.3 (+IN), R59.2, R60.2
OE#2: IC13.4 (EV/UVLO), Q9.1 (G); also elsewhere on the board
PE: C76.1, C83.1; also elsewhere on the board
PWM#2: IC13.22 (PWM), R71.2
Q6D: Q6.2 (D), Q6.4 (D), R54.2
SENSE1+1: C85.1, IC13.17 (SENSE+), R62.1
SENSE1-1: C85.2, IC13.16 (SENSE-), R63.1
SW2: C74.2, C78.1, D8.C, IC13.26 (SW), L4.1, Q7.3 (S), Q8.2 (D)
U_MON2: R68.1, R75.2; also elsewhere on the board
U_SET#2: R76.1; also elsewhere on the board
VOUT2+: C79.1, C80.1, C82.+, L5.1, R61.2, R67.2, R68.2, ZD4.A
VOUT_LC2+: C76.2, C77.1, C81.1 (+), CH2.TIP, J4.1, J4.1.1, L5.2, R69.1, ZD5.C
VREF2: C73.1, IC13.5 (VREF), IC13.10 (FBIN), IC13.13 (CTRL2), R78.2

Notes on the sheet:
Licensed under the TAPR Open Hardware License (www.tapr.org/OHL)
Repository: https://github.com/eez-open
More info at http://www.envox.hr/eez
CC mode detection
OE and CC indications
Power channel #2
